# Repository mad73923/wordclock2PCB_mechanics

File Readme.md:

## Todos
- NRST C?
- ESP GPIO2 Pullup?
- SD CS
- Crystals C?
- SD Card shield
⁻ no THT components due to wall mount!?
- PCB boarder <-> Trace 0.25mm
- C instead of Bat?
- User Button debounce like F746 Discovery
- USB next to SD

### Copper: 2oz!

- Check USART Bootloader Pin capability!!! http://www.st.com/content/ccc/resource/technical/document/application_note/b9/9b/16/3a/12/1e/40/0c/CD00167594.pdf/files/CD00167594.pdf/jcr:content/translations/en.CD00167594.pdf

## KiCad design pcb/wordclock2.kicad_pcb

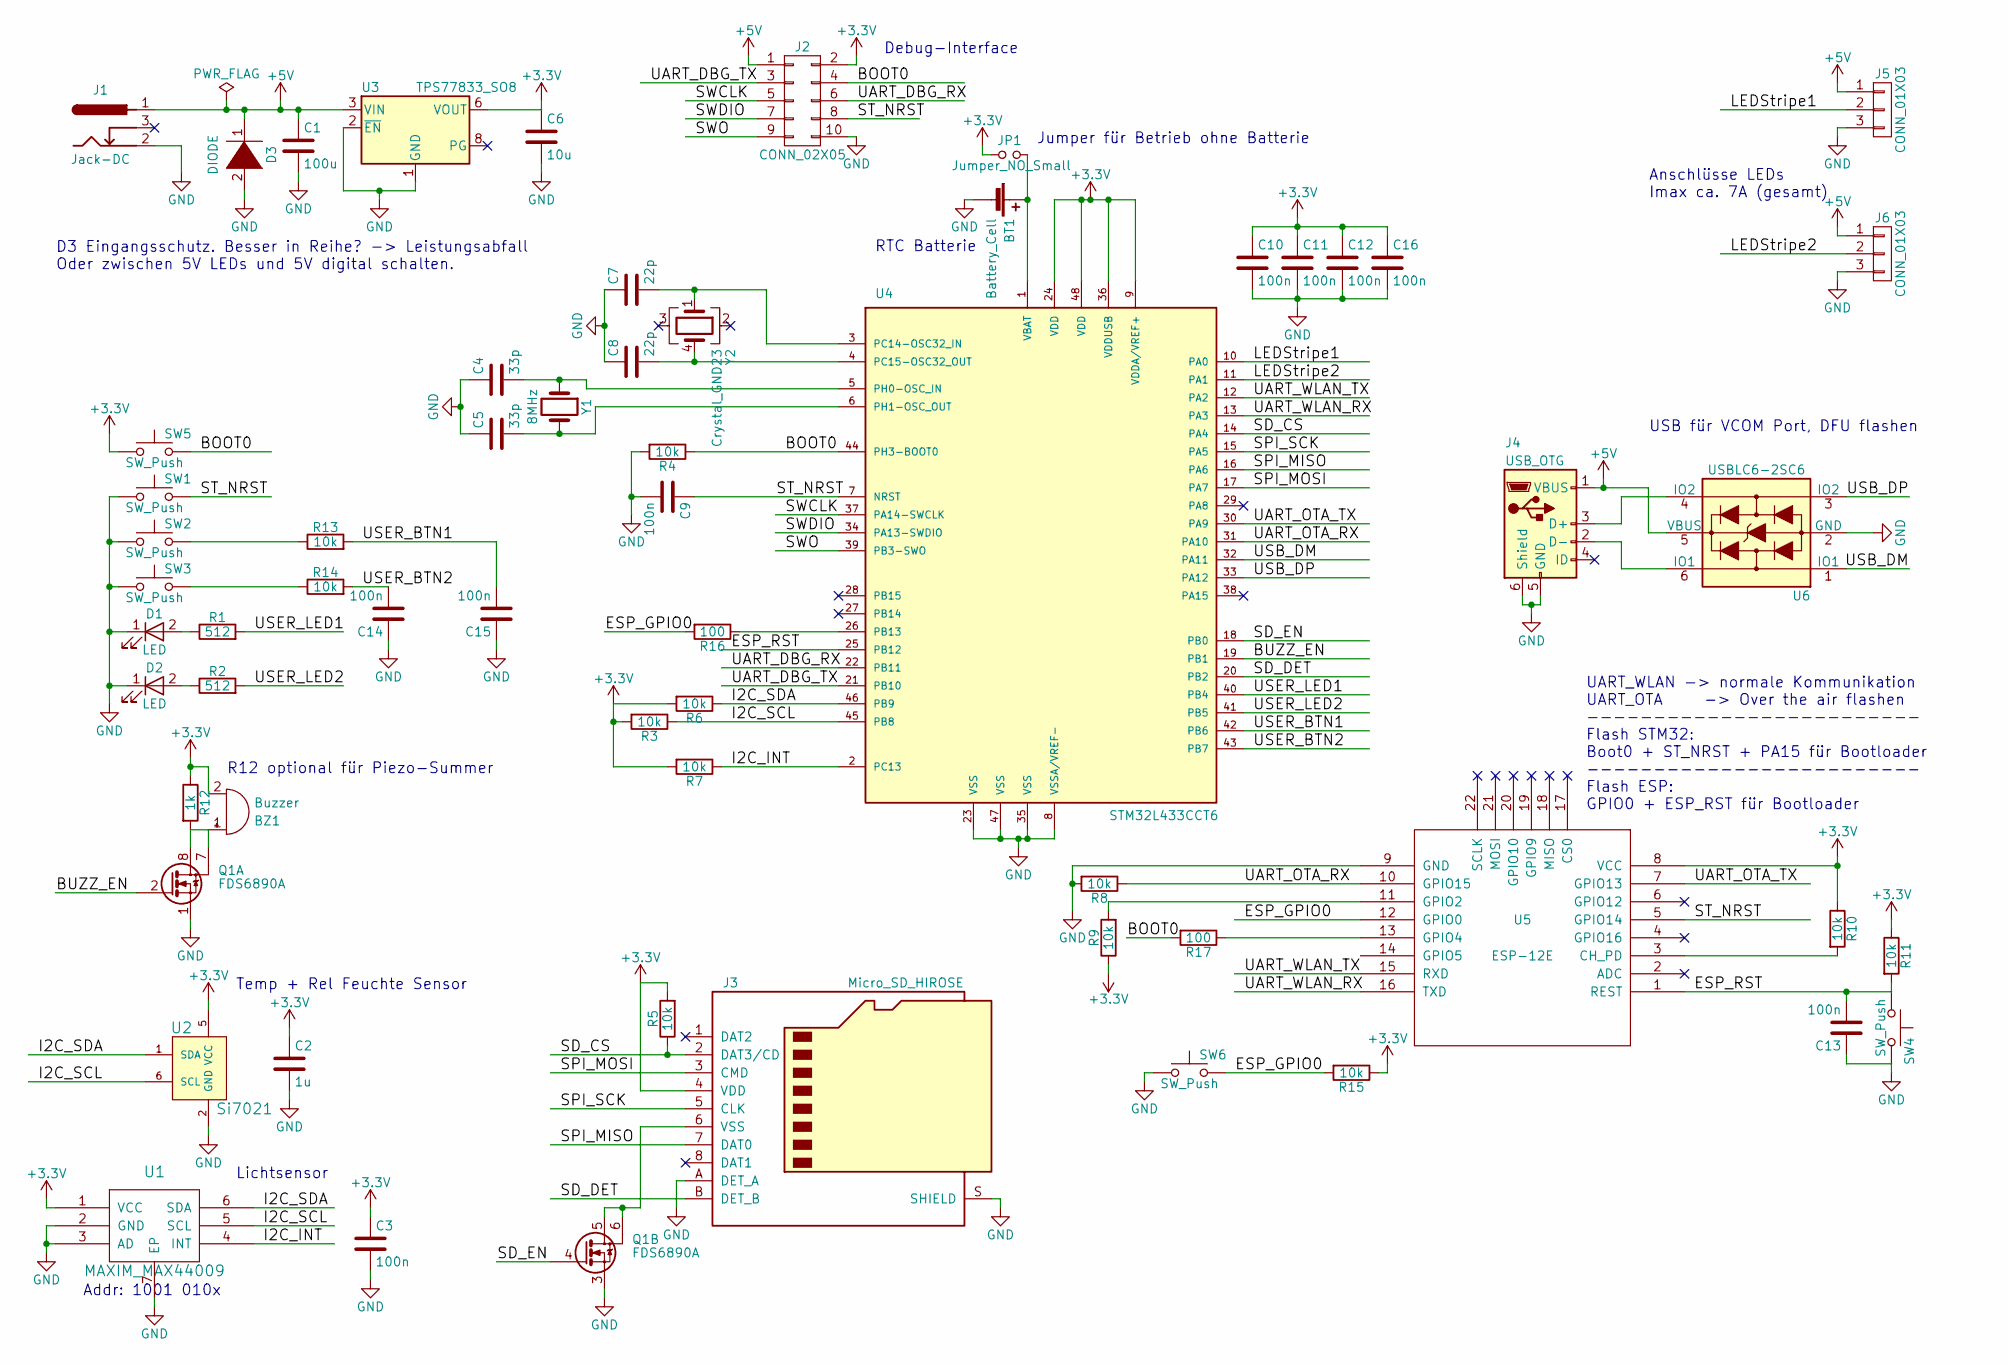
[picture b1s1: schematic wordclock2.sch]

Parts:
BT1: Battery_Cell; BK-890
BZ1: Buzzer; PKLCS1212E; Digi-Key 490-4683-1-ND
C1: 100u; CP_Tantalum_Case-D_EIA-7343-31_Hand
C2: 1u; C_0603_HandSoldering
C3, C9, C10, C11, C12, C13, C14, C15, C16: 100n; C_0603_HandSoldering
C4, C5: 33p; C_0603_HandSoldering
C6: 10u; C_0603_HandSoldering
C7, C8: 22p; C_0603_HandSoldering
D1, D2: LED; LED_0805_HandSoldering
D3: DIODE; D_PowerDI-123
J1: Jack-DC; BARREL_JACK
J2: CONN_02X05; SHF-105-01-L-D-RA
J3: Micro_SD_HIROSE; DM3D-SF
J4: USB_OTG; USB_Micro-B
J5, J6: CONN_01X03; CONN_HEADER_3POS
JP1: Jumper_NO_Small; SOLDER-JUMPER_1-WAY
Q1: FDS6890A; SOIC-8_3.9x4.9mm_Pitch1.27mm
R1, R2: 512; R_0603_HandSoldering
R3, R4, R5, R6, R7, R8, R9, R10, R11, R13, R14, R15: 10k; R_0603_HandSoldering
R12: 1k; R_0603_HandSoldering
R16, R17: 100; R_0603_HandSoldering
SW1, SW4, SW5, SW6: SW_Push; SW_SPST_KMR2
SW2, SW3: SW_Push; SW_Tactile_SPST_Angled_PTS645Vx39-2LFS
U1: MAXIM_MAX44009; MAX44009
U2: Si7021; Si7021-A20
U3: TPS77833_SO8; SOIC-8_3.9x4.9mm_Pitch1.27mm
U4: STM32L433CCT6; LQFP-48_7x7mm_Pitch0.5mm
U5: ESP-12E; ESP-12E_SMD
U6: USBLC6-2SC6; SOT-23-6
Y1: 8MHz; Crystal_SMD_HC49-SD_HandSoldering
Y2: Crystal_GND23; Crystal_SMD_SeikoEpson_MC306-4pin_8.0x3.2mm_HandSoldering

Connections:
+3V3: BZ1.2 (+), C2.1, C3.1, C6.1, C10.1, C11.1, C12.1, C16.1, J2.2, J3.4 (VDD), JP1.1, R3.2, R5.2, R6.2, R7.2, R9.1, R10.1, R11.1, R12.1, R15.1, SW5.1, U1.1 (VCC), U2.5 (VCC), U3.5 (VOUT), U3.6 (VOUT), U4.9 (VDDA/VREF+), U4.24 (VDD), U4.36 (VDDUSB), U4.48 (VDD), U5.8 (VCC)
+5V: C1.1, D3.1 (K), J1.1, J2.1, J4.1 (VBUS), J5.1, J6.1, U3.3 (VIN), U3.4 (VIN), U6.5 (VBUS)
/BOOT0: J2.4, R4.1, R17.2, SW5.2, U4.44 (PH3-BOOT0)
/BUZZ_EN: Q1.2 (G), U4.19 (PB1)
/ESP_GPIO0: R15.2, R16.2, SW6.2, U5.12 (GPIO0)
/ESP_RST: C13.2, R11.2, SW4.1, U4.25 (PB12), U5.1 (REST)
/I2C_INT: R7.1, U1.4 (INT), U4.2 (PC13)
/I2C_SCL: R3.1, U1.5 (SCL), U2.6 (SCL), U4.45 (PB8)
/I2C_SDA: R6.1, U1.6 (SDA), U2.1 (SDA), U4.46 (PB9)
/LEDStripe1: J5.2, U4.10 (PA0)
/LEDStripe2: J6.2, U4.11 (PA1)
/SD_CS: J3.2 (DAT3/CD), R5.1, U4.14 (PA4)
/SD_DET: J3.B (DET_B), U4.20 (PB2)
/SD_EN: Q1.4 (G), U4.18 (PB0)
/SPI_MISO: J3.7 (DAT0), U4.16 (PA6)
/SPI_MOSI: J3.3 (CMD), U4.17 (PA7)
/SPI_SCK: J3.5 (CLK), U4.15 (PA5)
/ST_NRST: C9.1, J2.8, SW1.2, U4.7 (NRST), U5.5 (GPIO14)
/SWCLK: J2.5, U4.37 (PA14-SWCLK)
/SWDIO: J2.7, U4.34 (PA13-SWDIO)
/SWO: J2.9, U4.39 (PB3-SWO)
/UART_DBG_RX: J2.6, U4.22 (PB11)
/UART_DBG_TX: J2.3, U4.21 (PB10)
/UART_OTA_RX: R8.1, U4.31 (PA10), U5.10 (GPIO15)
/UART_OTA_TX: U4.30 (PA9), U5.7 (GPIO13)
/UART_WLAN_RX: U4.13 (PA3), U5.16 (TXD)
/UART_WLAN_TX: U4.12 (PA2), U5.15 (RXD)
/USB_DM: U4.32 (PA11), U6.1 (IO1)
/USB_DP: U4.33 (PA12), U6.3 (IO2)
/USER_BTN1: C15.2, R13.2, U4.42 (PB6)
/USER_BTN2: C14.2, R14.2, U4.43 (PB7)
/USER_LED1: R1.2, U4.40 (PB4)
/USER_LED2: R2.2, U4.41 (PB5)
GND: BT1.2 (-), C1.2, C2.2, C3.2, C4.1, C5.1, C6.2, C7.1, C8.1, C9.2, C10.2, C11.2, C12.2, C13.1, C14.1, C15.1, C16.2, D1.1 (K), D2.1 (K), D3.2 (A), J1.2, J2.10, J3.A (DET_A), J3.S (SHIELD), J4.5 (GND), J4.6 (Shield), J5.3, J6.3, Q1.1 (S), Q1.3 (S), R4.2, R8.2, SW1.1, SW2.1, SW3.1, SW4.2, SW6.1, U1.2 (GND), U1.3 (AD), U1.7 (EP), U2.2 (GND), U3.1 (GND), U3.2 (~EN~), U4.8 (VSSA/VREF-), U4.23 (VSS), U4.35 (VSS), U4.47 (VSS), U5.9 (GND), U6.2 (GND)
unnamed: BT1.1 (+), JP1.2, U4.1 (VBAT)
unnamed: BZ1.1 (-), Q1.7, Q1.8 (D), R12.2
unnamed: C4.2, U4.5 (PH0-OSC_IN), Y1.1
unnamed: C5.2, U4.6 (PH1-OSC_OUT), Y1.2
unnamed: C7.2, U4.3 (PC14-OSC32_IN), Y2.1
unnamed: C8.2, U4.4 (PC15-OSC32_OUT), Y2.4
unnamed: D1.2 (A), R1.1
unnamed: D2.2 (A), R2.1
unnamed: J3.6 (VSS), Q1.5 (D), Q1.6
unnamed: J4.2 (D-), U6.6 (IO1)
unnamed: J4.3 (D+), U6.4 (IO2)
unnamed: R9.2, U5.11 (GPIO2)
unnamed: R10.2, U5.3 (CH_PD)
unnamed: R13.1, SW2.2
unnamed: R14.1, SW3.2
unnamed: R16.1, U4.26 (PB13)
unnamed: R17.1, U5.13 (GPIO4)

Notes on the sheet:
Addr: 1001 010x
D3 Eingangsschutz. Besser in Reihe? -> Leistungsabfall Oder zwischen 5V LEDs und 5V digital schalten.
Jumper für Betrieb ohne Batterie
Anschlüsse LEDs Imax ca. 7A (gesamt)
Debug-Interface
R12 optional für Piezo-Summer
Temp + Rel Feuchte Sensor
Lichtsensor
UART_WLAN -> normale Kommunikation UART_OTA -> Over the air flashen ------------------------- Flash STM32: Boot0 + ST_NRST + PA15 für Bootloader ------------------------- Flash ESP: GPIO0 + ESP_RST für Bootloader
USB für VCOM Port, DFU flashen
RTC Batterie

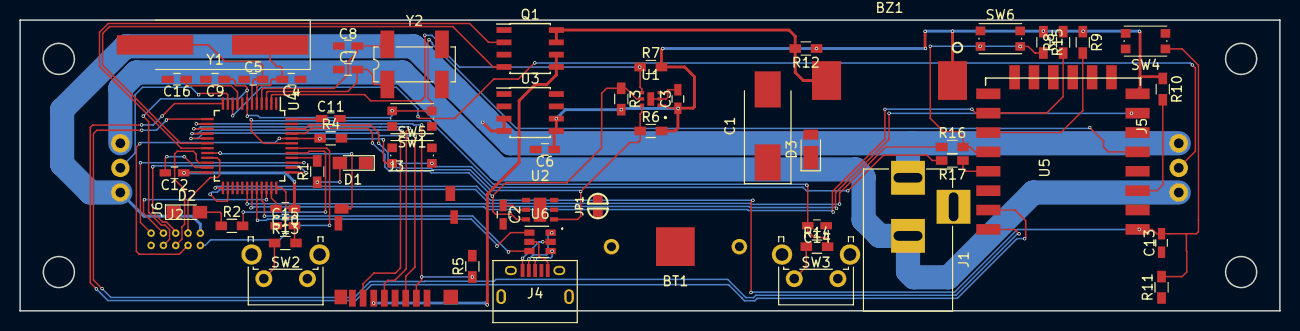
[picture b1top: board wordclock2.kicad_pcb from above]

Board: 2 copper layers, 130.0 x 30.0 mm, 60 parts (0 on the bottom side), 51 nets.

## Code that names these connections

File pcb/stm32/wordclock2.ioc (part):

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Mcu.Name=STM32L433C(B-C)Tx
Mcu.Package=LQFP48
Mcu.UserName=STM32L433CCTx
PA0.GPIOParameters=GPIO_Label
PA0.GPIO_Label=LEDStripe1
PA0.Signal=S_TIM2_CH1
PA1.GPIOParameters=GPIO_Label
PA1.GPIO_Label=LEDStripe2
PA1.Signal=S_TIM2_CH2
PA10.GPIOParameters=GPIO_Label
PA10.GPIO_Label=UART_OTA_RX
PA10.Mode=Asynchronous
PA10.Signal=USART1_RX
PA11.Mode=Device
PA11.Signal=USB_DM
PA12.Mode=Device
PA12.Signal=USB_DP
PA13\ (JTMS-SWDIO).Mode=Trace_Asynchronous_SW
PA13\ (JTMS-SWDIO).Signal=SYS_JTMS-SWDIO
PA14\ (JTCK-SWCLK).Mode=Trace_Asynchronous_SW
PA14\ (JTCK-SWCLK).Signal=SYS_JTCK-SWCLK
PA2.GPIOParameters=GPIO_Label
PA2.GPIO_Label=UART_WLAN_TX
PA2.Mode=Asynchronous
PA2.Signal=USART2_TX
PA3.GPIOParameters=GPIO_Label
PA3.GPIO_Label=UART_WLAN_RX
PA3.Mode=Asynchronous
PA3.Signal=USART2_RX
PA4.GPIOParameters=GPIO_Label
PA4.GPIO_Label=SD_CS
PA4.Signal=GPIO_Output
PA5.Mode=Full_Duplex_Master
PA5.Signal=SPI1_SCK
PA6.Mode=Full_Duplex_Master
PA6.Signal=SPI1_MISO
PA7.Mode=Full_Duplex_Master
PA7.Signal=SPI1_MOSI
PA9.GPIOParameters=GPIO_Label
PA9.GPIO_Label=UART_OTA_TX
PA9.Mode=Asynchronous
PA9.Signal=USART1_TX
PB0.GPIOParameters=GPIO_Label
PB0.GPIO_Label=SD_EN
PB0.Signal=GPIO_Output
PB1.GPIOParameters=GPIO_Label
PB1.GPIO_Label=BUZZ_EN
PB1.Signal=GPIO_Output
PB10.GPIOParameters=GPIO_Label
PB10.GPIO_Label=UART_DBG_TX
PB10.Mode=Asynchronous
PB10.Signal=USART3_TX
PB11.GPIOParameters=GPIO_Label
PB11.GPIO_Label=UART_DBG_RX
PB11.Mode=Asynchronous
PB11.Signal=USART3_RX
PB12.GPIOParameters=GPIO_Label
PB12.GPIO_Label=ESP_RST
PB12.Signal=GPIO_Output
PB13.GPIOParameters=GPIO_Label
PB13.GPIO_Label=ESP_GPIO0
PB13.Signal=GPIO_Output
PB2.GPIOParameters=GPIO_Label
PB2.GPIO_Label=SD_DET
PB2.Signal=GPXTI2
PB3\ (JTDO-TRACESWO).Mode=Trace_Asynchronous_SW
PB3\ (JTDO-TRACESWO).Signal=SYS_JTDO-SWO
PB4\ (NJTRST).GPIOParameters=GPIO_Label
PB4\ (NJTRST).GPIO_Label=USER_LED1
PB4\ (NJTRST).Signal=GPIO_Output
PB5.GPIOParameters=GPIO_Label
PB5.GPIO_Label=USER_LED2
PB5.Signal=GPIO_Output
PB6.GPIOParameters=GPIO_Label
PB6.GPIO_Label=USER_BTN1
PB6.Signal=GPXTI6
PB7.GPIOParameters=GPIO_Label
PB7.GPIO_Label=USER_BTN2
PB7.Signal=GPXTI7
PB8.Mode=I2C
PB8.Signal=I2C1_SCL
PB9.Mode=I2C
PB9.Signal=I2C1_SDA
PC13.GPIOParameters=GPIO_Label
PC13.GPIO_Label=I2C_INT
PC13.Signal=GPXTI13
PC14-OSC32_IN\ (PC14).Mode=LSE-External-Oscillator
PC14-OSC32_IN\ (PC14).Signal=RCC_OSC32_IN
PC15-OSC32_OUT\ (PC15).Mode=LSE-External-Oscillator
PC15-OSC32_OUT\ (PC15).Signal=RCC_OSC32_OUT
PH0-OSC_IN\ (PH0).Mode=HSE-External-Oscillator
PH0-OSC_IN\ (PH0).Signal=RCC_OSC_IN
PH1-OSC_OUT\ (PH1).Mode=HSE-External-Oscillator
PH1-OSC_OUT\ (PH1).Signal=RCC_OSC_OUT
RCC.HSE_VALUE=8000000
RCC.SYSCLKFreq_VALUE=80000000
RCC.SYSCLKSource=RCC_SYSCLKSOURCE_PLLCLK

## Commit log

2017-06-17 Initialer Commit
2017-08-02 progress
2017-08-02 rm submodules
2017-08-02 proper submodules
2017-08-05 added datasheets
2017-08-06 rescued scad file
2017-08-06 annotated schematic
2017-09-02 progres, new footprint, datasheet
2017-10-22 battery
2017-10-28 progress, added 32kHz Crystal datasheet
2017-10-28 smaller battery mount
2017-12-18 first traces
2017-12-18 deleted submodul, added resistor on GPIO line
2017-12-18 changed to 0603 components, added schematic notes
2017-12-18 drawing notes, moved hole lines to fab layer
2017-12-18 adapted library path
2017-12-21 added resistor in series BOOT0, button protection
2017-12-21 updated sd-card detection pad
2017-12-21 added supercap to BOM, user button datasheet
2017-12-25 first tracks
2018-01-01 ESD Diodes USB, many tracks, huge progress
